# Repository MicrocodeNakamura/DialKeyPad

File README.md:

# DialKeyPad
ダイアルとキーを持つデバイスのファームウェア

# 追加方法
pico-examplesフォルダに回答したdevelopフォルダを格納する。<BR>
pico-examplesフォルダのCMakeLists.txt 末尾に以下の行を追加する。<BR>
add_subdirectory(develop)<BR>

pico-examplesフォルダでcmake -S. -B build を実行する。<BR>
pico-examples/developフォルダでmake を実行する。<BR>

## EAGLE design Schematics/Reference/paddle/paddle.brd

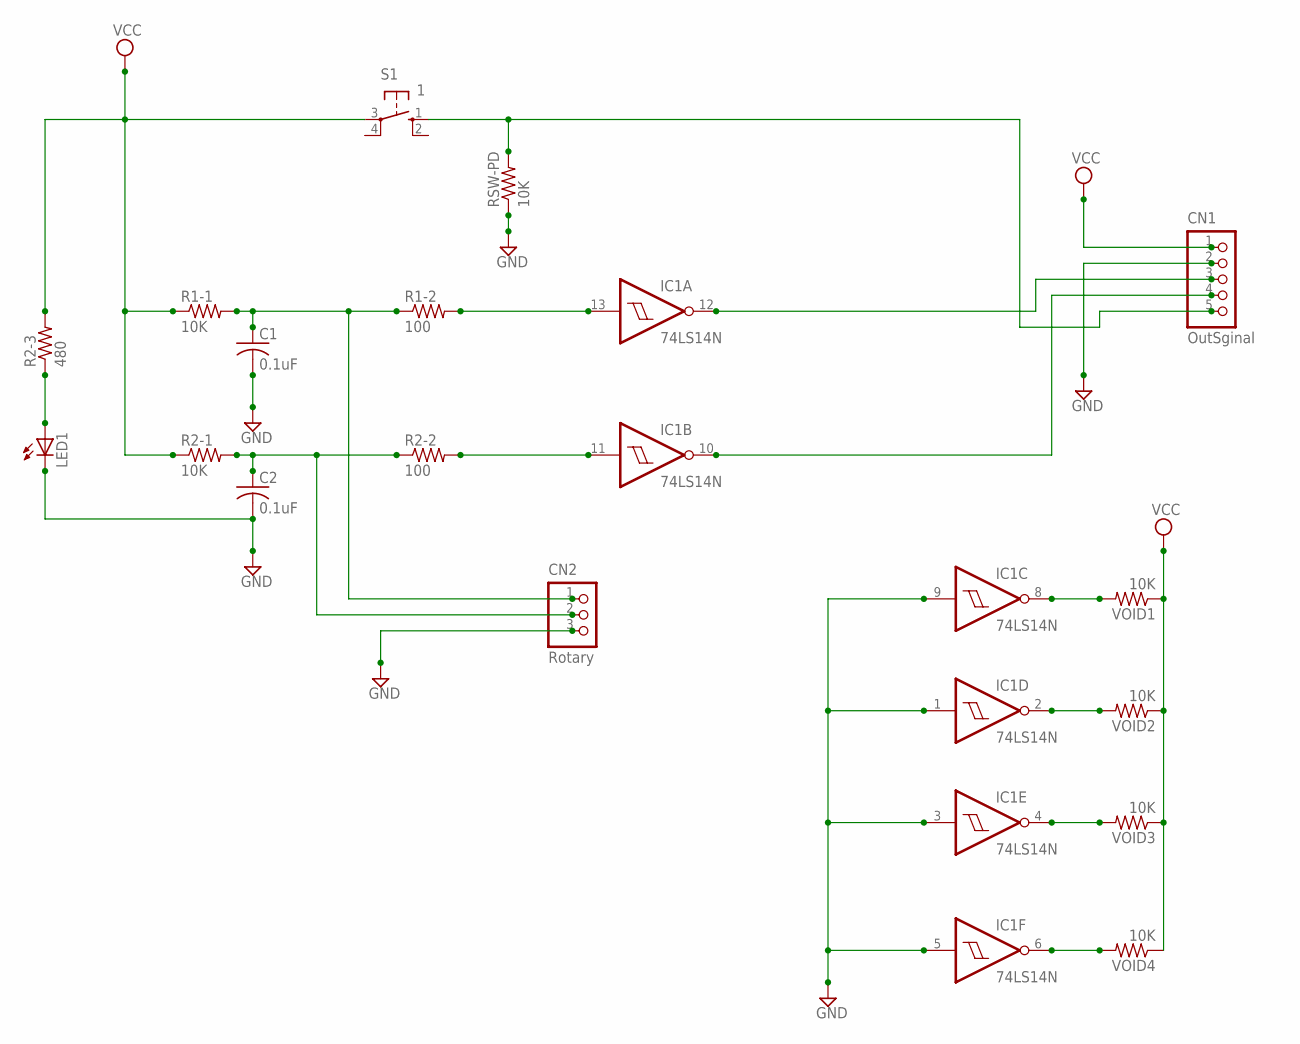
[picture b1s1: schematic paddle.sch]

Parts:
C1, C2: 0.1uF; C050-050X075
CN1: OutSginal; B5B-PH-K-S
CN2: Rotary; B3B-PH-K-S
IC1: 74LS14N; DIL14
LED1: LED3MM
R1-1, R2-1: 10K; 0207/2V
R1-2, R2-2: 100; 0207/2V
R2-3: 480; 0207/2V
RSW-PD: 10K; 0207/2V
S1: 1; B3F-10XX
VOID1, VOID2, VOID3, VOID4: 10K; 0207/2V

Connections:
GND: C1.2, C2.2, CN1.2, CN2.3, IC1.1 (I), IC1.3 (I), IC1.5 (I), IC1.7 (GND), IC1.9 (I), LED1.K (C), RSW-PD.1
unnamed: C1.1, CN2.1, R1-1.2, R1-2.1
unnamed: IC1.13 (I), R1-2.2
unnamed: C2.1, CN2.2, R2-1.2, R2-2.1
unnamed: IC1.11 (I), R2-2.2
unnamed: IC1.8 (O), VOID1.2
unnamed: IC1.2 (O), VOID2.2
unnamed: IC1.4 (O), VOID3.2
unnamed: IC1.6 (O), VOID4.2
unnamed: CN1.5, RSW-PD.2, S1.1 (S)
unnamed: CN1.3, IC1.12 (O)
unnamed: CN1.4, IC1.10 (O)
unnamed: LED1.A, R2-3.1
VCC: CN1.1, IC1.14 (VCC), R1-1.1, R2-1.1, R2-3.2, S1.3, VOID1.1, VOID2.1, VOID3.1, VOID4.1

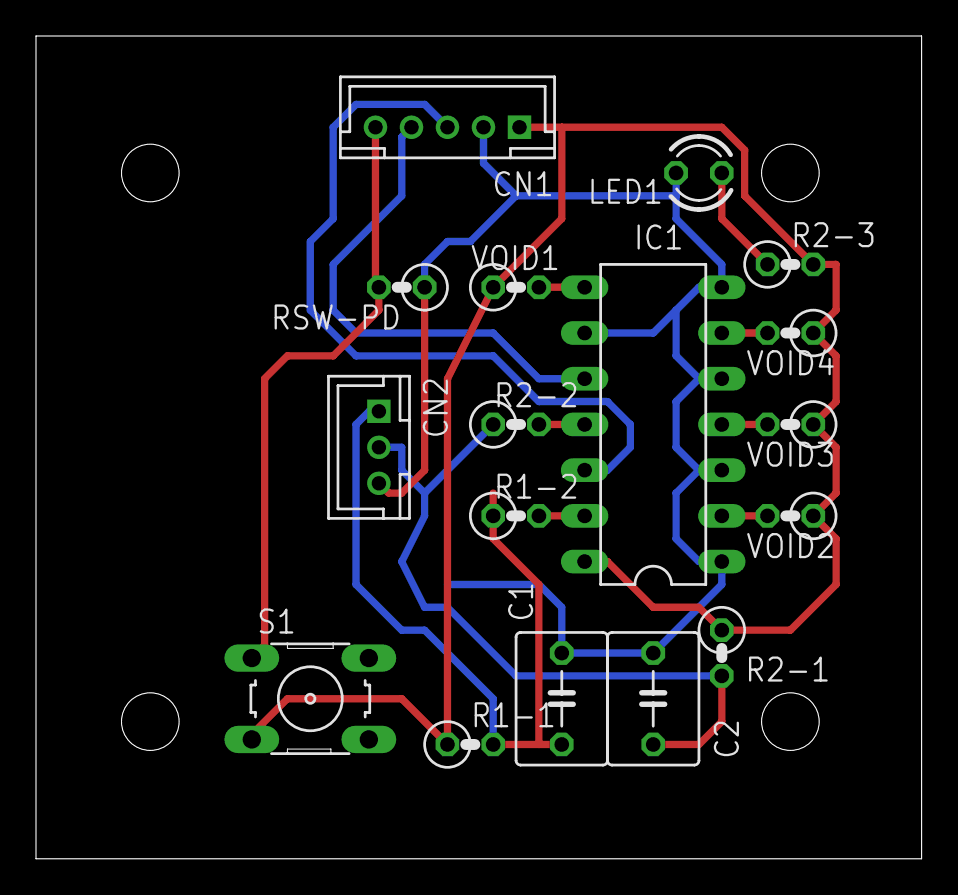
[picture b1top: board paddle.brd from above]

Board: 2 copper layers, 49.2 x 45.7 mm, 17 parts (0 on the bottom side), 14 nets.

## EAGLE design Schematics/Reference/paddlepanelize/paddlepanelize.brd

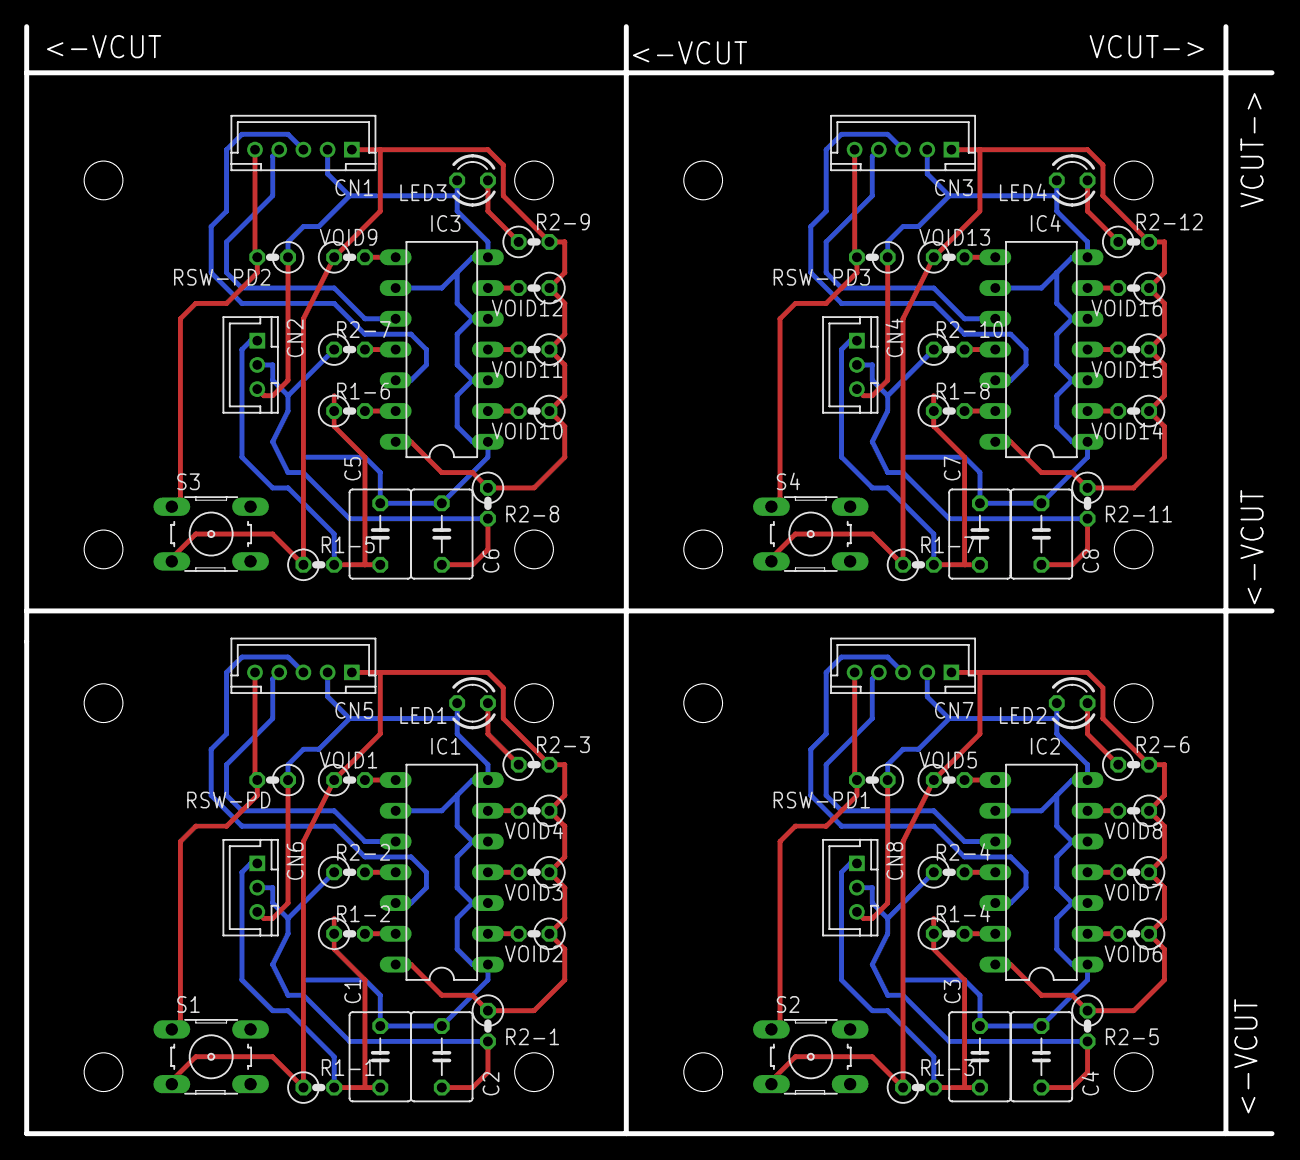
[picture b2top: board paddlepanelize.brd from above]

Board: 2 copper layers, 103.0 x 91.4 mm, 68 parts (0 on the bottom side), 56 nets.

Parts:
C1, C2, C3, C4, C5, C6, C7, C8: 0.1uF; C050-050X075
CN1, CN3, CN5, CN7: OutSginal; B5B-PH-K-S
CN2, CN4, CN6, CN8: Rotary; B3B-PH-K-S
IC1, IC2, IC3, IC4: 74LS14N; DIL14
LED1, LED2, LED3, LED4: LED3MM
R1-1, R1-3, R1-5, R1-7, R2-1, R2-5, R2-8, R2-11: 10K; 0207/2V
R1-2, R1-4, R1-6, R1-8, R2-2, R2-4, R2-7, R2-10: 100; 0207/2V
R2-3, R2-6, R2-9, R2-12: 480; 0207/2V
RSW-PD, RSW-PD1, RSW-PD2, RSW-PD3: 10K; 0207/2V
S1, S2, S3, S4: 1; B3F-10XX
VOID1, VOID2, VOID3, VOID4, VOID5, VOID6, VOID7, VOID8, VOID9, VOID10, VOID11, VOID12, VOID13, VOID14, VOID15, VOID16: 10K; 0207/2V

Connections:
GND: C1.2, C2.2, CN5.2, CN6.3, IC1.1, IC1.3, IC1.5, IC1.7, IC1.9, LED1.K, RSW-PD.1
GND1: C3.2, C4.2, CN7.2, CN8.3, IC2.1, IC2.3, IC2.5, IC2.7, IC2.9, LED2.K, RSW-PD1.1
GND2: C5.2, C6.2, CN1.2, CN2.3, IC3.1, IC3.3, IC3.5, IC3.7, IC3.9, LED3.K, RSW-PD2.1
GND3: C7.2, C8.2, CN3.2, CN4.3, IC4.1, IC4.3, IC4.5, IC4.7, IC4.9, LED4.K, RSW-PD3.1
unnamed: C1.1, CN6.1, R1-1.2, R1-2.1
unnamed: IC1.13, R1-2.2
unnamed: C2.1, CN6.2, R2-1.2, R2-2.1
unnamed: IC1.11, R2-2.2
unnamed: IC1.8, VOID1.2
unnamed: IC1.2, VOID2.2
unnamed: IC1.4, VOID3.2
unnamed: IC1.6, VOID4.2
unnamed: CN5.5, RSW-PD.2, S1.1
unnamed: CN5.3, IC1.12
unnamed: CN5.4, IC1.10
unnamed: LED1.A, R2-3.1
unnamed: C3.1, CN8.1, R1-3.2, R1-4.1
unnamed: IC2.13, R1-4.2
unnamed: C4.1, CN8.2, R2-4.1, R2-5.2
unnamed: IC2.11, R2-4.2
unnamed: IC2.8, VOID5.2
unnamed: IC2.2, VOID6.2
unnamed: IC2.4, VOID7.2
unnamed: IC2.6, VOID8.2
unnamed: CN7.5, RSW-PD1.2, S2.1
unnamed: CN7.3, IC2.12
unnamed: CN7.4, IC2.10
unnamed: LED2.A, R2-6.1
unnamed: C5.1, CN2.1, R1-5.2, R1-6.1
unnamed: IC3.13, R1-6.2
unnamed: C6.1, CN2.2, R2-7.1, R2-8.2
unnamed: IC3.11, R2-7.2
unnamed: IC3.8, VOID9.2
unnamed: IC3.2, VOID10.2
unnamed: IC3.4, VOID11.2
unnamed: IC3.6, VOID12.2
unnamed: CN1.5, RSW-PD2.2, S3.1
unnamed: CN1.3, IC3.12
unnamed: CN1.4, IC3.10
unnamed: LED3.A, R2-9.1
unnamed: C7.1, CN4.1, R1-7.2, R1-8.1
unnamed: IC4.13, R1-8.2
unnamed: C8.1, CN4.2, R2-10.1, R2-11.2
unnamed: IC4.11, R2-10.2
unnamed: IC4.8, VOID13.2
unnamed: IC4.2, VOID14.2
unnamed: IC4.4, VOID15.2
unnamed: IC4.6, VOID16.2
unnamed: CN3.5, RSW-PD3.2, S4.1
unnamed: CN3.3, IC4.12
unnamed: CN3.4, IC4.10
unnamed: LED4.A, R2-12.1
VCC: CN5.1, IC1.14, R1-1.1, R2-1.1, R2-3.2, S1.3, VOID1.1, VOID2.1, VOID3.1, VOID4.1
VCC1: CN7.1, IC2.14, R1-3.1, R2-5.1, R2-6.2, S2.3, VOID5.1, VOID6.1, VOID7.1, VOID8.1
VCC2: CN1.1, IC3.14, R1-5.1, R2-8.1, R2-9.2, S3.3, VOID9.1, VOID10.1, VOID11.1, VOID12.1
VCC3: CN3.1, IC4.14, R1-7.1, R2-11.1, R2-12.2, S4.3, VOID13.1, VOID14.1, VOID15.1, VOID16.1

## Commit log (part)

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2026-05-31 Add Old scematics for reference.
2026-05-31 Add Schematics PDF
2026-05-31 Del scematics files.
2026-05-31 Add requirement and architecture document
2026-06-07 add prototype code has added.
2026-06-07 Chg develop folder install instruction added.
2026-06-07 Chg develop folder install instruction added one more.
2026-06-21 CUIインターフェースとNVMの領域確保
    コマンドはNULLしか追加していない
2026-06-28 Flashメモリ消去、書き込みドライバの追加
2026-06-28 ソースコードを個別に追加
